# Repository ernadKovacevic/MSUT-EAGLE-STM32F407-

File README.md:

# msut-EAGLE-STM32F407-

Final project : Controling WS2812b diodes 

https://github.com/Indir99/MSUT-controlling-ws2812b-diodes

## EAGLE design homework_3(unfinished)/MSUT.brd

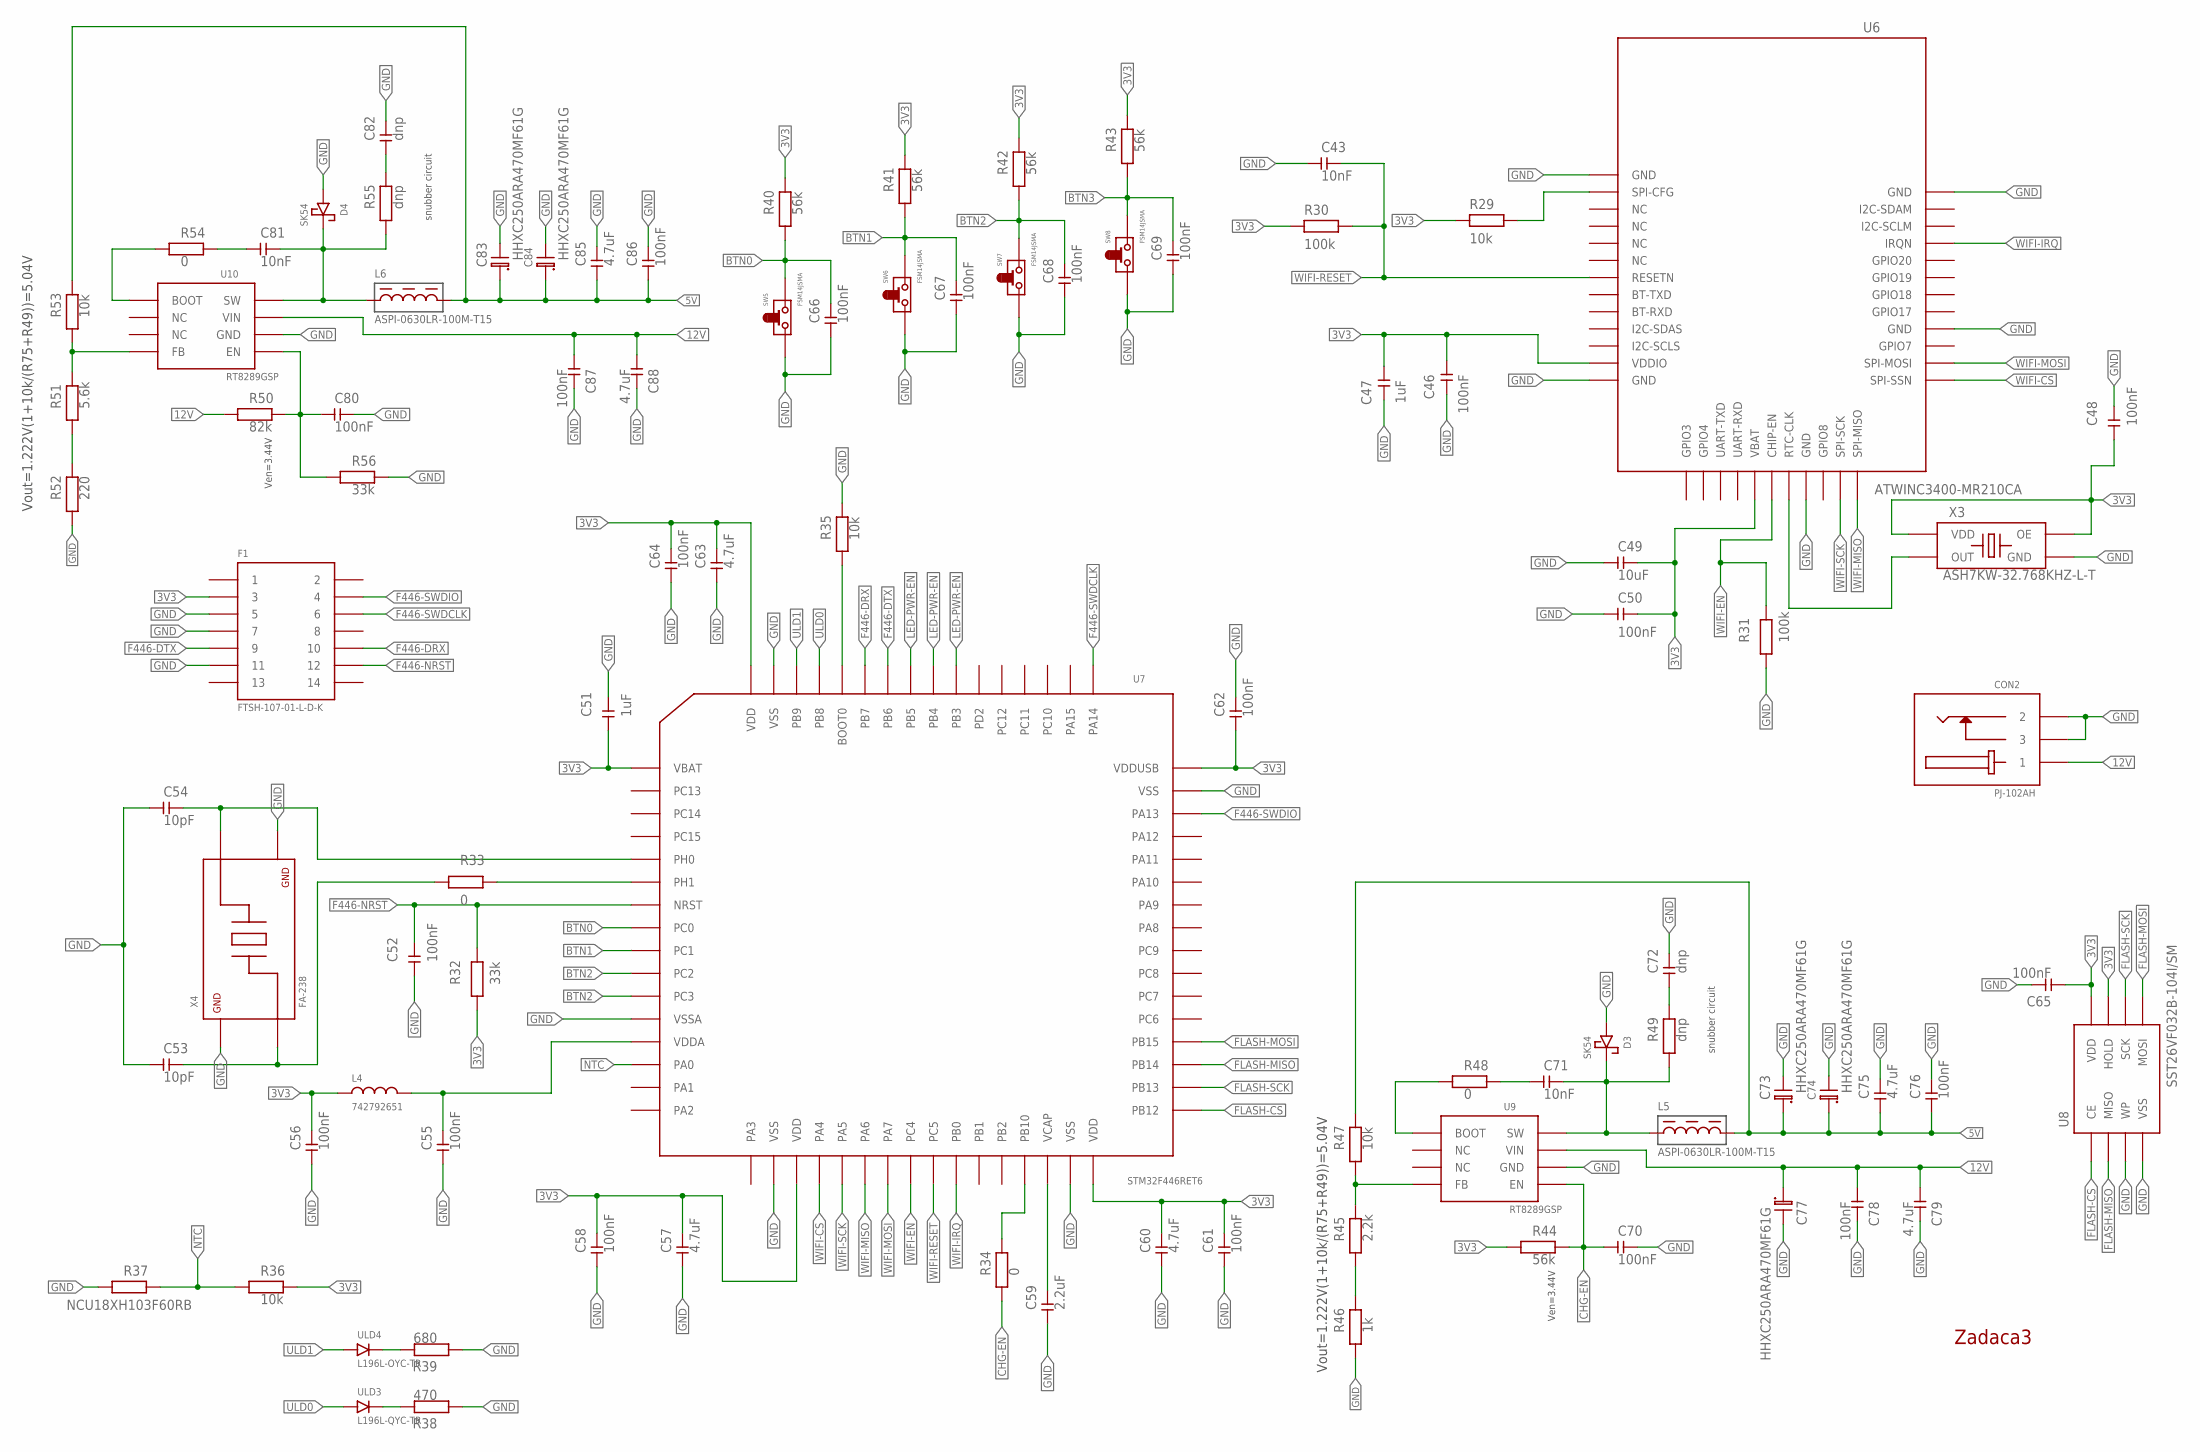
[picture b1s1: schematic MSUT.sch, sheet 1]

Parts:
C43, C71, C81: 10nF; PACKAGE_0805
C46, C48, C50, C52, C55, C56, C58, C61, C62, C64, C65, C66, C67, C68, C69, C70, C76, C78, C80, C86, C87: 100nF; PACKAGE_0805
C47, C51: 1uF; PACKAGE_0805
C49: 10uF; PACKAGE_0805
C53, C54: 10pF; PACKAGE_0805
C57, C60, C63, C75, C79, C85, C88: 4.7uF; PACKAGE_0805
C59: 2.2uF; PACKAGE_0805
C72, C82: dnp; PACKAGE_0805
C73, C74, C83, C84: HHXC250ARA470MF61G; PACKAGE_EL_CAP_HXC
C77: HHXB350ARA470MF61G; PACKAGE_EL_CAP_HXC
CON2: PJ-102AH; TRAY_PJ-102AH
D3, D4: SK54; D0-214AB
F1: FTSH-107-01-L-D-K; TUBE_FTSH-107-01-L-D-K
L4: 742792651; PACKAGE_0805
L5, L6: ASPI-0630LR-100M-T15; PACKAGE_ASPI-0630
R29, R35, R36, R47, R53: 10k; PACKAGE_0805
R30, R31: 100k; PACKAGE_0805
R32, R56: 33k; PACKAGE_0805
R33, R34, R48, R54: 0; PACKAGE_0805
R37: NCU18XH103F60RB; PACKAGE_0805
R38: 470; PACKAGE_0805
R39: 680; PACKAGE_0805
R40, R41, R42, R43, R44: 56k; PACKAGE_0805
R45: 2.2k; PACKAGE_0805
R46: 1k; PACKAGE_0805
R49, R55: dnp; PACKAGE_0805
R50: 82k; PACKAGE_0805
R51: 5.6k; PACKAGE_0805
R52: 220; PACKAGE_0805
SW5, SW6, SW7, SW8: FSM14JSMA
U6: NETWORK_CONTROLLER; PACKAGE_ATWINC3400-MR210XA
U7: STM32F446RET6; TRAY_STM32F446RET6
U8: SST26VF032B-104I/SM; 8-SOIJ
U9, U10: RT8289GSP; 8-SOIC
ULD3: L196L-QYC-TR; TAPE&REEL_DIODE
ULD4: L196L-OYC-TR; TAPE&REEL_DIODE
X3: ASH7KW-32.768KHZ-L-T; PACKAGE_ASH7KW
X4: FA-238; PACKAGE_FA-23816.0000MB-K0

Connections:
3V3: C46.P1, C47.P1, C48.P1, C49.P2, C50.P2, C51.P1, C56.P2, C57.P2, C58.P2, C60.P2, C61.P2, C62.P1, C63.P2, C64.P2, C65.P1, F1.3, L4.P1 (PIN1), R29.P1, R30.P1, R32.P1, R36.P2, R40.P2, R41.P2, R42.P2, R43.P2, R44.P1, U6.VBAT, U6.VDDIO, U7.VBAT, U7.VDD1 (VDD), U7.VDD2 (VDD), U7.VDD3 (VDD), U7.VDDUSB, U8.HOLD, U8.VDD, X3.OE, X3.VDD
5V: C73.P1, C74.P1, C75.P1, C76.P1, C83.P1, C84.P1, C85.P1, C86.P1, L5.PIN2, L6.PIN2, R47.P2, R53.P2; also elsewhere on the board
12V: C77.P1, C78.P1, C79.P1, C87.P1, C88.P1, CON2.1, R50.P1, U9.VIN, U10.VIN
BTN0: C66.P2, R40.P1, SW5.3 (PIN2), SW5.4 (PIN2), U7.PC0
BTN1: C67.P2, R41.P1, SW6.3 (PIN2), SW6.4 (PIN2), U7.PC1
BTN2: C68.P2, R42.P1, SW7.3 (PIN2), SW7.4 (PIN2), U7.PC2, U7.PC3
BTN3: C69.P2, R43.P1, SW8.3 (PIN2), SW8.4 (PIN2)
CHG-EN: C70.P1, C80.P1, R34.P1, R44.P2, R50.P2, R56.P1, U9.EN, U10.EN
F446-DRX: F1.10, U7.PB7
F446-DTX: F1.9, U7.PB6
F446-NRST: C52.P2, F1.12, R32.P2, U7.NRST
F446-SWDCLK: F1.6, U7.PA14
F446-SWDIO: F1.4, U7.PA13
FLASH-CS: U7.PB12, U8.CE
FLASH-MISO: U7.PB14, U8.MISO
FLASH-MOSI: U7.PB15, U8.MOSI
FLASH-SCK: U7.PB13, U8.SCK
GND: C43.P1, C46.P2, C47.P2, C48.P2, C49.P1, C50.P1, C51.P2, C52.P1, C53.P1, C54.P1, C55.P1, C56.P1, C57.P1, C58.P1, C59.P1, C60.P1, C61.P1, C62.P2, C63.P1, C64.P1, C65.P2, C66.P1, C67.P1, C68.P1, C69.P1, C70.P2, C72.P2, C73.P2, C74.P2, C75.P2, C76.P2, C77.P2, C78.P2, C79.P2, C80.P2, C82.P2, C83.P2, C84.P2, C85.P2, C86.P2, C87.P2, C88.P2, CON2.2, CON2.3, D3.ANODE, D4.ANODE, F1.5, F1.7, F1.11, R31.P1, R35.P2, R37.P1, R38.P1, R39.P1, R46.P1, R52.P1, R56.P2, SW5.1 (PIN1), SW5.2 (PIN1), SW6.1 (PIN1), SW6.2 (PIN1), SW7.1 (PIN1), SW7.2 (PIN1), SW8.1 (PIN1), SW8.2 (PIN1), U6.GND@1 (GND), U6.GND@2 (GND), U6.GND@3 (GND), U6.GND@4 (GND), U6.GND@5 (GND), U6.GND@6 (GND), U7.VSS1 (VSS), U7.VSS2 (VSS), U7.VSS3 (VSS), U7.VSS4 (VSS), U7.VSSA, U8.VSS, U8.WP, U9.GND1 (GND), U9.GND2 (GND), U10.GND1 (GND), U10.GND2 (GND), X3.GND, X4.2 (GND), X4.4 (GND); also elsewhere on the board
LED-PWR-EN: U7.PB3, U7.PB4, U7.PB5
unnamed: R29.P2, U6.SPI-CFG
unnamed: U6.RTC-CLK, X3.OUT
unnamed: R33.P2, U7.PH1
unnamed: C53.P2, R33.P1, X4.1 (PIN1)
unnamed: C54.P2, U7.PH0, X4.3 (PIN2)
unnamed: C55.P2, L4.P2 (PIN2), U7.VDDA
unnamed: R34.P2, U7.PB10
unnamed: C59.P2, U7.VCAP
unnamed: R35.P1, U7.BOOT0
unnamed: R38.P2, ULD3.CATHODE
unnamed: R39.P2, ULD4.CATHODE
unnamed: R45.P2, R47.P1, U9.FB
unnamed: R45.P1, R46.P2
unnamed: C71.P1, R48.P2
unnamed: R48.P1, U9.BOOT
unnamed: C71.P2, D3.CATHODE, L5.PIN1, R49.P1, U9.SW
unnamed: C72.P1, R49.P2
unnamed: R51.P2, R53.P1, U10.FB
unnamed: R51.P1, R52.P2
unnamed: C81.P1, R54.P2
unnamed: R54.P1, U10.BOOT
unnamed: C81.P2, D4.CATHODE, L6.PIN1, R55.P1, U10.SW
unnamed: C82.P1, R55.P2
NTC: R36.P1, R37.P2, U7.PA0
ULD0: U7.PB8, ULD3.ANODE
ULD1: U7.PB9, ULD4.ANODE
WIFI-CS: U6.SPI-SSN, U7.PA4
WIFI-EN: R31.P2, U6.CHIP-EN, U7.PC4
WIFI-IRQ: U6.IRQN, U7.PB0
WIFI-MISO: U6.SPI-MISO, U7.PA6
WIFI-MOSI: U6.SPI-MOSI, U7.PA7
WIFI-RESET: C43.P2, R30.P2, U6.RESETN, U7.PC5
WIFI-SCK: U6.SPI-SCK, U7.PA5

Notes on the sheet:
Zadaca3
Ven=3.44V
snubber circuit
Vout=1.222V(1+10k/(R75+R49))=5.04V

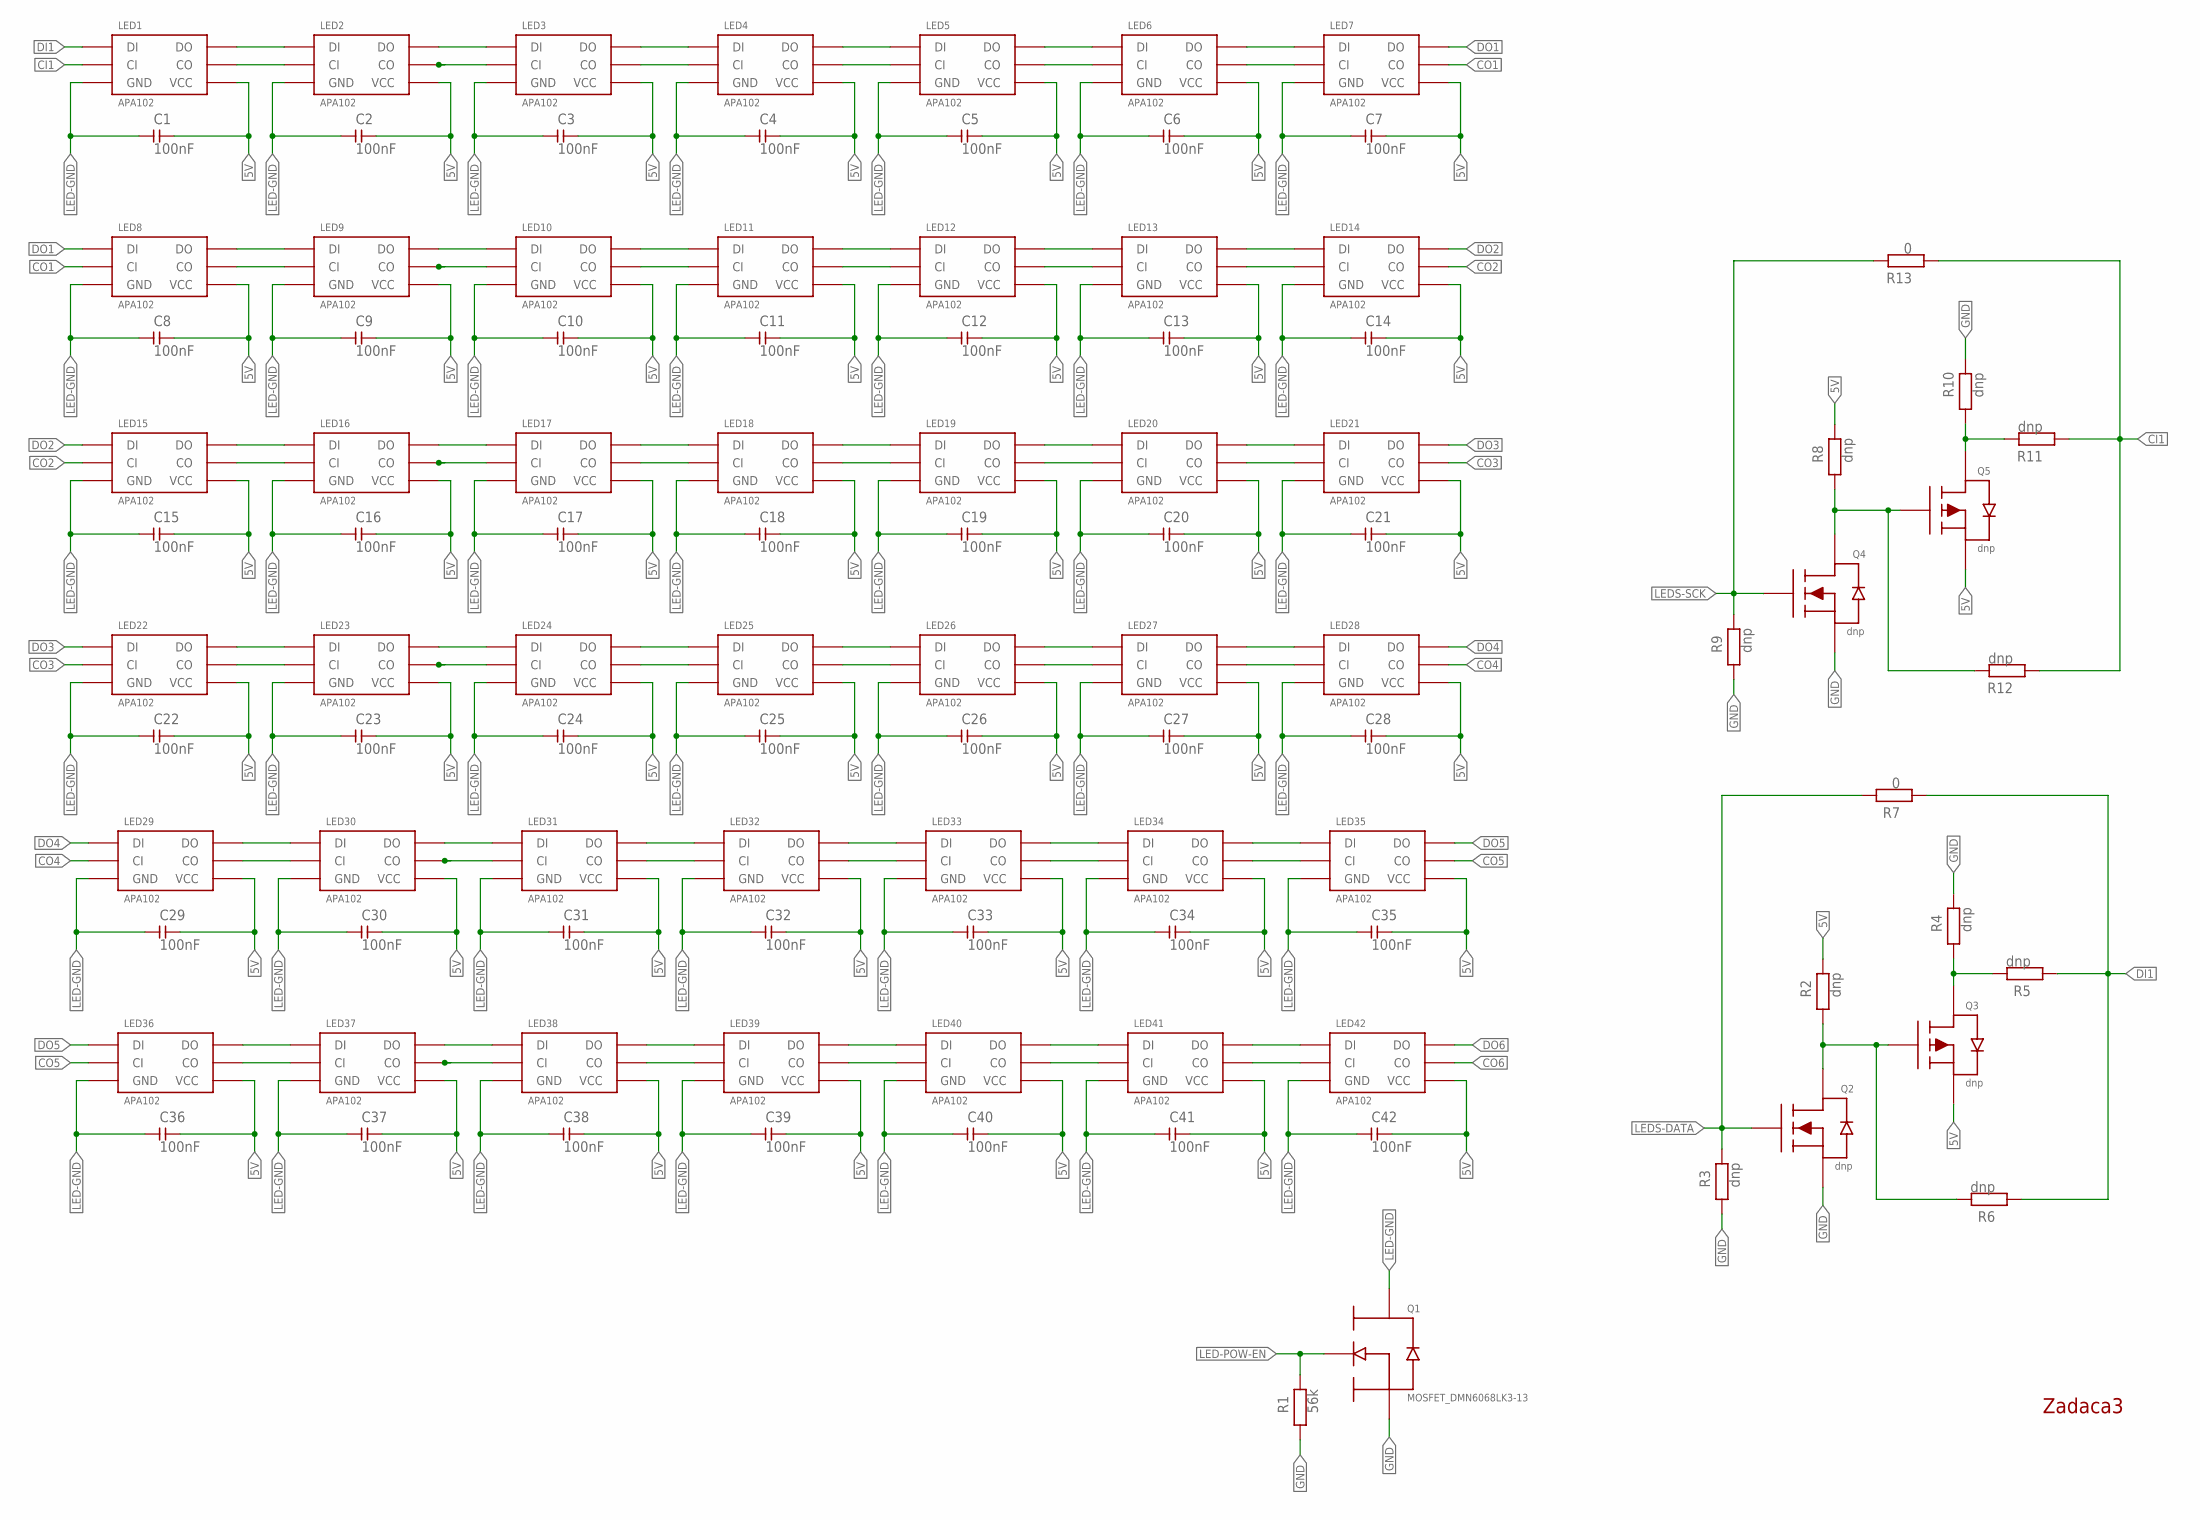
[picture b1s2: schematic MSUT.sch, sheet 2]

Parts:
C1, C2, C3, C4, C5, C6, C7, C8, C9, C10, C11, C12, C13, C14, C15, C16, C17, C18, C19, C20, C21, C22, C23, C24, C25, C26, C27, C28, C29, C30, C31, C32, C33, C34, C35, C36, C37, C38, C39, C40, C41, C42: 100nF; PACKAGE_0805
LED1, LED2, LED3, LED4, LED5, LED6, LED7, LED8, LED9, LED10, LED11, LED12, LED13, LED14, LED15, LED16, LED17, LED18, LED19, LED20, LED21, LED22, LED23, LED24, LED25, LED26, LED27, LED28, LED29, LED30, LED31, LED32, LED33, LED34, LED35, LED36, LED37, LED38, LED39, LED40, LED41, LED42: RGB_LED; TAPE&REEL_LED
Q1: MOSFET_DMN6068LK3-13; TO252-3L
Q2, Q4: NCHANNEL_MOSFET; SOT-23-3
Q3, Q5: PCHANNEL_MOSFET; SOT-23-3
R1: 56k; PACKAGE_0805
R2, R3, R4, R5, R6, R8, R9, R10, R11, R12: dnp; PACKAGE_0805
R7, R13: 0; PACKAGE_0805

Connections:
5V: C1.P2, C2.P2, C3.P2, C4.P2, C5.P2, C6.P2, C7.P2, C8.P2, C9.P2, C10.P2, C11.P2, C12.P2, C13.P2, C14.P2, C15.P2, C16.P2, C17.P2, C18.P2, C19.P2, C20.P2, C21.P2, C22.P2, C23.P2, C24.P2, C25.P2, C26.P2, C27.P2, C28.P2, C29.P2, C30.P2, C31.P2, C32.P2, C33.P2, C34.P2, C35.P2, C36.P2, C37.P2, C38.P2, C39.P2, C40.P2, C41.P2, C42.P2, LED1.VDD (VCC), LED2.VDD (VCC), LED3.VDD (VCC), LED4.VDD (VCC), LED5.VDD (VCC), LED6.VDD (VCC), LED7.VDD (VCC), LED8.VDD (VCC), LED9.VDD (VCC), LED10.VDD (VCC), LED11.VDD (VCC), LED12.VDD (VCC), LED13.VDD (VCC), LED14.VDD (VCC), LED15.VDD (VCC), LED16.VDD (VCC), LED17.VDD (VCC), LED18.VDD (VCC), LED19.VDD (VCC), LED20.VDD (VCC), LED21.VDD (VCC), LED22.VDD (VCC), LED23.VDD (VCC), LED24.VDD (VCC), LED25.VDD (VCC), LED26.VDD (VCC), LED27.VDD (VCC), LED28.VDD (VCC), LED29.VDD (VCC), LED30.VDD (VCC), LED31.VDD (VCC), LED32.VDD (VCC), LED33.VDD (VCC), LED34.VDD (VCC), LED35.VDD (VCC), LED36.VDD (VCC), LED37.VDD (VCC), LED38.VDD (VCC), LED39.VDD (VCC), LED40.VDD (VCC), LED41.VDD (VCC), LED42.VDD (VCC), Q3.SOURCE, Q5.SOURCE, R2.P2, R8.P2; also elsewhere on the board
CI1: LED1.CI, R11.P1, R12.P1, R13.P1
CO1: LED7.CO, LED8.CI
CO2: LED14.CO, LED15.CI
CO3: LED21.CO, LED22.CI
CO4: LED28.CO, LED29.CI
CO5: LED35.CO, LED36.CI
CO6: LED42.CO
DI1: LED1.DI, R5.P1, R6.P1, R7.P1
DO1: LED7.DO, LED8.DI
DO2: LED14.DO, LED15.DI
DO3: LED21.DO, LED22.DI
DO4: LED28.DO, LED29.DI
DO5: LED35.DO, LED36.DI
DO6: LED42.DO
GND: Q1.DRAIN, Q2.SOURCE, Q4.SOURCE, R1.P1, R3.P1, R4.P2, R9.P1, R10.P2; also elsewhere on the board
LED-GND: C1.P1, C2.P1, C3.P1, C4.P1, C5.P1, C6.P1, C7.P1, C8.P1, C9.P1, C10.P1, C11.P1, C12.P1, C13.P1, C14.P1, C15.P1, C16.P1, C17.P1, C18.P1, C19.P1, C20.P1, C21.P1, C22.P1, C23.P1, C24.P1, C25.P1, C26.P1, C27.P1, C28.P1, C29.P1, C30.P1, C31.P1, C32.P1, C33.P1, C34.P1, C35.P1, C36.P1, C37.P1, C38.P1, C39.P1, C40.P1, C41.P1, C42.P1, LED1.GND, LED2.GND, LED3.GND, LED4.GND, LED5.GND, LED6.GND, LED7.GND, LED8.GND, LED9.GND, LED10.GND, LED11.GND, LED12.GND, LED13.GND, LED14.GND, LED15.GND, LED16.GND, LED17.GND, LED18.GND, LED19.GND, LED20.GND, LED21.GND, LED22.GND, LED23.GND, LED24.GND, LED25.GND, LED26.GND, LED27.GND, LED28.GND, LED29.GND, LED30.GND, LED31.GND, LED32.GND, LED33.GND, LED34.GND, LED35.GND, LED36.GND, LED37.GND, LED38.GND, LED39.GND, LED40.GND, LED41.GND, LED42.GND, Q1.SOURCE
LED-POW-EN: Q1.GATE, R1.P2
LEDS-DATA: Q2.GATE, R3.P2, R7.P2
LEDS-SCK: Q4.GATE, R9.P2, R13.P2
unnamed: LED1.DO, LED2.DI
unnamed: LED1.CO, LED2.CI
unnamed: LED2.DO, LED3.DI
unnamed: LED2.CO, LED3.CI
unnamed: LED3.DO, LED4.DI
unnamed: LED3.CO, LED4.CI
unnamed: LED4.DO, LED5.DI
unnamed: LED4.CO, LED5.CI
unnamed: LED5.DO, LED6.DI
unnamed: LED5.CO, LED6.CI
unnamed: LED6.DO, LED7.DI
unnamed: LED6.CO, LED7.CI
unnamed: LED8.DO, LED9.DI
unnamed: LED8.CO, LED9.CI
unnamed: LED9.DO, LED10.DI
unnamed: LED9.CO, LED10.CI
unnamed: LED10.DO, LED11.DI
unnamed: LED10.CO, LED11.CI
unnamed: LED11.DO, LED12.DI
unnamed: LED11.CO, LED12.CI
unnamed: LED12.DO, LED13.DI
unnamed: LED12.CO, LED13.CI
unnamed: LED13.DO, LED14.DI
unnamed: LED13.CO, LED14.CI
unnamed: LED15.DO, LED16.DI
unnamed: LED15.CO, LED16.CI
unnamed: LED16.DO, LED17.DI
unnamed: LED16.CO, LED17.CI
unnamed: LED17.DO, LED18.DI
unnamed: LED17.CO, LED18.CI
unnamed: LED18.DO, LED19.DI
unnamed: LED18.CO, LED19.CI
unnamed: LED19.DO, LED20.DI
unnamed: LED19.CO, LED20.CI
unnamed: LED20.DO, LED21.DI
unnamed: LED20.CO, LED21.CI
unnamed: LED22.DO, LED23.DI
unnamed: LED22.CO, LED23.CI
unnamed: LED23.DO, LED24.DI
unnamed: LED23.CO, LED24.CI
unnamed: LED24.DO, LED25.DI
unnamed: LED24.CO, LED25.CI
unnamed: LED25.DO, LED26.DI
unnamed: LED25.CO, LED26.CI
unnamed: LED26.DO, LED27.DI
unnamed: LED26.CO, LED27.CI
unnamed: LED27.DO, LED28.DI
unnamed: LED27.CO, LED28.CI
unnamed: LED29.DO, LED30.DI
unnamed: LED29.CO, LED30.CI
unnamed: LED30.DO, LED31.DI
unnamed: LED30.CO, LED31.CI
unnamed: LED31.DO, LED32.DI
unnamed: LED31.CO, LED32.CI
unnamed: LED32.DO, LED33.DI
unnamed: LED32.CO, LED33.CI
unnamed: LED33.DO, LED34.DI
unnamed: LED33.CO, LED34.CI
unnamed: LED34.DO, LED35.DI
unnamed: LED34.CO, LED35.CI
unnamed: LED36.DO, LED37.DI
unnamed: LED36.CO, LED37.CI
unnamed: LED37.DO, LED38.DI
unnamed: LED37.CO, LED38.CI
unnamed: LED38.DO, LED39.DI
unnamed: LED38.CO, LED39.CI
unnamed: LED39.DO, LED40.DI
unnamed: LED39.CO, LED40.CI
unnamed: LED40.DO, LED41.DI
unnamed: LED40.CO, LED41.CI
unnamed: LED41.DO, LED42.DI
unnamed: LED41.CO, LED42.CI
unnamed: Q2.DRAIN, Q3.GATE, R2.P1, R6.P2
unnamed: Q3.DRAIN, R4.P1, R5.P2
unnamed: Q4.DRAIN, Q5.GATE, R8.P1, R12.P2
unnamed: Q5.DRAIN, R10.P1, R11.P2

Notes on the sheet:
Zadaca3

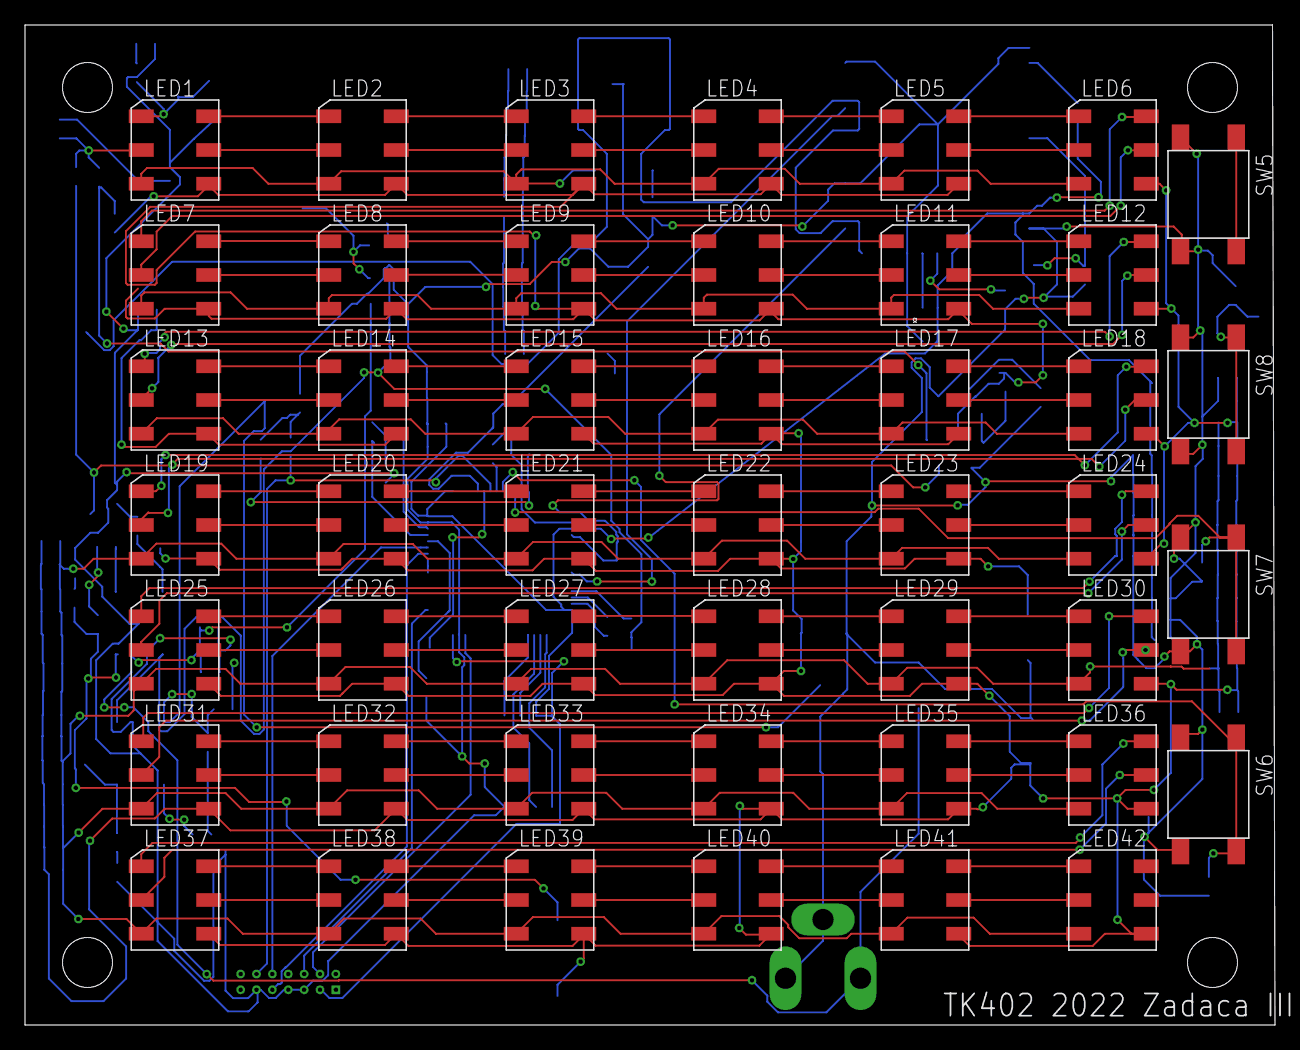
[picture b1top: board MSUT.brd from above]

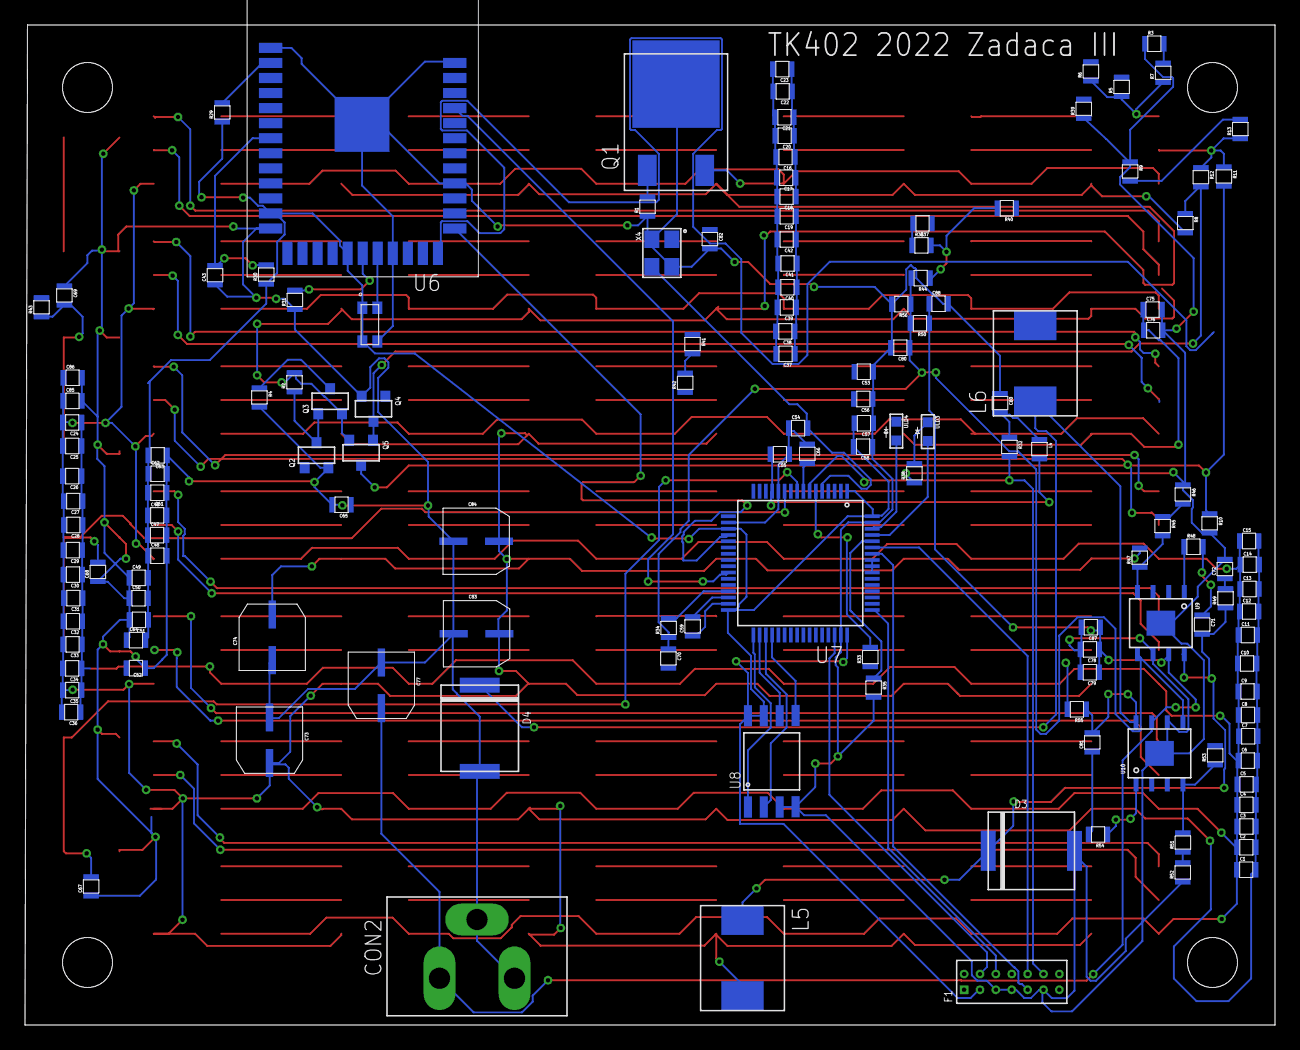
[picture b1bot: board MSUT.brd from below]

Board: 2 copper layers, 100.0 x 80.0 mm, 194 parts (148 on the bottom side), 144 nets.

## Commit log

2022-03-06 homework2021/2022
